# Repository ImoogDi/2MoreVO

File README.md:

#  2MoreVO
 Eurorack Dual VCO using the public CEM3340/AS3340 chip.

**Table of Contents**

- [Introduction](#intro)
- [Construction Guide](./doc/constructionguide.md)
- [Calibration](./doc/calibration.md)
- [Technical data](#technical-data)
- [References](#references)
- [License](#license)

## Introduction

This eurorack-modul is designed for modular-synthesizers as dual Voltage Controlled Oscillator.  
The oszillators are build around two IC's: <u>AS3340</u>, a clone of that wellknown CEM3340.  
Another benifit is the <u>three cannel VCA: AS3363</u> included to control the modulation-level, waveform output of VCO1 and oscillator-signal fading between VCO1- and VCO2-outputs.  

The '2MoreVO'-PCB's are:  
- one main backplane ('Backplane'), holding all switches, pots, jacks and voltage-references.  
- two VCO-PCB's stacked on the 'Backplane'.  
- one another backplane-PCB ('Backplane_B') hodling the 'three cannel VCA', operational-amp's and the eurorack-connection stacked on the 'Backplane'.   

All parts are common available and DIY-friendly designed, most parts are SMD on the VCO-PCB's.   
(Details see attached pictures)  

- Modul Frontpanel

<br>
- Modul Backpanel

<br>
- Modul function-blocks

<br>

<hr>
There are twelve 3.5mm jacks available for patching audio- and CV-signals.  

<table>
<tr>
    <th>Jack-Name</th>
    <th>Function</th>
    <th>Comment</th>
    <th>Detail</th>
</tr>
<tr>
    <td>1V/Oct CV1</td>
    <td>CV-input for VCO1 pitch control</td>
    <td>fixed 1Volt/Octave scaling</td>
    <td>This input is normalised with the eurobus Control-Voltage and connected with the '1V/Oct CV2' input.<br>Patch-cabel plugged in breaks the default connection to eurobus CV but the connection to '1V/Oct CV2' is still available.</td>
</tr>
<tr>
    <td>Fade CV</td>
    <td>CV-input for fading oscillator-signals</td>
    <td>The Fading between Osc1- and Osc2-signals on 'Osc-Mix Out' is controlled with this CV</td>
    <td>CV level adjustable between 0 ... max. with 'Fade CV'-pot.<br>works together with 'Osc-Fade'-pot.<hr>Bipolar signal input.</td>
</tr>
<tr>
    <td>Wave1 CV</td>
    <td>CV-input for VCO1 wave-control</td>
    <td>The waveform on 'Osc1 Out' is controlled with this CV</td>
    <td>CV Level adjustable between 0 ... max. with 'Wave1 CV'-pot.<hr>Bipolar signal input.</td>
</tr>
<tr>
    <td>Mod.Level CV</td>
    <td>CV-input for modulation level control</td>
    <td>Control of modulation level on 'Mod Out'</td>
    <td>Modulation Level adjustable between 0 ... max. with 'Mod.Level CV'-pot.<hr>Bipolar signal input.</td>
</tr>
<tr>
    <td>Mod. In</td>
    <td>Modulation signal input</td>
    <td>input for external signals controlling FM(Lin/Log) and PWM on Osc1 and Osc2</td>
    <td>This input is normalised with the sinusoidal-signal from Osc2 if no signal is plugged in.<hr>Bipolar signal input.</td>
</tr>
<tr>
    <td>1V/Oct CV2</td>
    <td>CV-input for VCO2 pitch control</td>
    <td>fixed 1Volt/Octave scaling</td>
    <td>This input is normalised with the '1V/Oct CV1' input.<br>Patch-cabel plugged in breaks the default connection to '1V/Oct CV1'.</td>
</tr>
<tr>
    <td>Osc1 Out</td>
    <td>output for VCO1-oscillator signal</td>
    <td>triangle- to saw-waveform output, morvable manually or with external CV</td>
    <td>Waveform morvable with 'Wave1 CV'-pot and CV-signal.</td>
</tr>
<tr>
    <td>Osc-Mix Out</td>
    <td>output for mixed VCO1-/VCO2-oscillator signal</td>
    <td>mixed signal from Osc1- and Osc2-outputs</td>
    <td>Waveforms fadeable between Osc1- and Osc2-signal outputs.<br>Fading can be done with 'Fade CV'-pot and CV-signal.<br>50%/50% Osc1/2-signal level on 'Osc-Mix Out', if 'Osc-Fade'-pot is in centerposition and no 'Fade CV' is plugged in.</td>
</tr>
<tr>
    <td>Osc2 Out</td>
    <td>output for VCO2-oscillator signal</td>
    <td>saw- to triangle-waveform output, morvable manually</td>
    <td>Waveform morvable with 'Wave2'-pot between saw- and triangle-signal.</td>
</tr>
<tr>
    <td>Sync In</td>
    <td>Sync-signal for VCO1 (optional VCO2)</td>
    <td>this signal can be switched to: 'Sync Hard', ' Sync Soft' or 'Off'</td>
    <td>This input is normalised with the 'Puls2 Out'-signal from VCO2.<br>Patch-cabel plugged in breaks the default connection to 'Puls2 Out'.</td>
</tr>
<tr>
    <td>Mod Out</td>
    <td>output for modulation-signal controllable with 'Mod.Level CV'</td>
    <td>modulation-signal used for 'FMx Lin/Log' and 'PWM'<br>default sinusoidal-signal from VCO2 used for VCO1 modulation</td>
    <td>sinusoidal-signal from VCO2 is available on this output if high impedance connection is used.<hr>optional an external low impedance signal plugged in can overwride the internal modulation.</td>
</tr>
<tr>
    <td>Puls2 Out</td>
    <td>output for puls-signal from VCO2</td>
    <td>output-signal for synchronisation and audio<br>the pulswith is controllable with 'PWM'-pot using the 'Mod Out'-signal</td>
    <td>This output is also internally linked to 'Sync In'.<hr>Bipolar output with +-5.0Volt level.</td>
</tr>
</table>
<br>

There are eight potentiometers with following functions:  

<table>
<tr>
    <th>Pot-Name</th>
    <th>Function</th>
    <th>Comment</th>
    <th>Detail</th>
</tr>
<tr>
    <td>Tune 1</td>
    <td>Pitch for VCO1</td>
    <td>default pitch in center-position</td>
    <td>tuning-range +-2 octaves.</td>
</tr>
<tr>
    <td>Tune 2</td>
    <td>Pitch for VCO2</td>
    <td>default pitch in center-position</td>
    <td>tuning-range +-2 octaves.</td>
</tr>
<tr>
    <td>Osc-Fade</td>
    <td>manually fading between Osc1- and Osc2-signals on 'Osc-Mix Out'</td>
    <td>works as CV offset for the 'Fade CV'-signal</td>
    <td>pot to CCW: Osc2-signal output.<br>pot to CW: Osc1-signal output.<br>pot to centerposition: equal level output.</td>
</tr>
<tr>
    <td>Fade CV</td>
    <td>CV Level amount pot for fading between Osc1- and Osc2-signals on 'Osc-Mix Out'</td>
    <td>works together with 'Osc-Fade' for fading Osc1/2-signals</td>
    <td>CV Level adjustable between 0 ... max.</td>
</tr>
<tr>
    <td>Wave1 CV</td>
    <td>CV Level amount pot for Osc1 waveform-selection on 'Osc1 out'</td>
    <td>manually selection of waveform is possible if no CV-signal is plugged in</td>
    <td>CV Level adjustable between 0 ... max.</td>
</tr>
<tr>
    <td>Mod.Level CV</td>
    <td>CV Level amount pot for modulation control</td>
    <td>manually modulationlevel control is possible if no CV-signal is plugged in</td>
    <td>CV Level adjustable between 0 ... max.</td>
</tr>
<tr>
    <td>PWM</td>
    <td>pulswith pot to control amount of PWM</td>
    <td>the modulation-signal on 'Mod Out' is used for PWM</td>
    <td>PWM amount adjustable between 0 ... max.<br>Pulswith is 50% on 'Puls2 Out' if pot is in CCW-position (set to 0).</td>
</tr>
<tr>
    <td>Wave2</td>
    <td>waveform selection pot for Osc2-signal</td>
    <td>manually morving between saw- and triangle-signal</td>
    <td>pot to CCW: SAW-signal.<br>pot to CW: Triangle-signal.<br>pot to centerposition: mixed signal.</td>
</tr>
</table>
<br>

There are six switches to control the behaviour of signals.  

<table>
<tr>
    <th>Switch</th>
    <th>Function</th>
    <th>Comment</th>
    <th>Detail</th>
</tr>
<tr>
    <td>FM1-switch</td>
    <td>switch for VCO1 FM modulation using signal on 'Mod Out'</td>
    <td>FM controll for VCO1</td>
    <td>FM1 Lin := Linear FM modulation.<br>Off := function off.<br>FM1 Log := Logarithmic FM modulation.</td>
</tr>
<tr>
    <td>Sync-switch</td>
    <td>switch for VCO1 Hard- or Soft-synchronisation with puls-signal from VCO2</td>
    <td>switched synchronisation-signal from 'Puls2 Out'</td>
    <td>Sync Hard := hard synced to VCO2.<br>Off := sync. function off.<br>Sync Soft := soft synced to VCO2.</td>
</tr>
<tr>
    <td>VCO1 Octave-switch</td>
    <td>switch for VCO1 pitch setting</td>
    <td>octaves up or down depending on 'Octave switch + or -'</td>
    <td>1 := one octave (up/down).<br>2 := two octaves (up/down).</td>
</tr>
<tr>
    <td>Octave up/down switch</td>
    <td>switch for VCO1- and VCO2-switched pitchcontrol</td>
    <td>selecting pitch up or down for VCO1 and VCO2</td>
    <td>+ :=  pitch up.<br>- := pitch down.</td>
</tr>
<tr>
    <td>VCO2 Octave-switch</td>
    <td>switch for VCO2 pitch setting</td>
    <td>octaves up or down depending on 'Octave switch + or -'</td>
    <td>1 := one octave (up/down).<br>2 := two octaves (up/down).</td>
</tr>
<tr>
    <td>FM2-switch</td>
    <td>switch for VCO2 FM modulation using signal on 'Mod Out'</td>
    <td>FM controll for VCO2</td>
    <td>FM1 Lin := Linear FM modulation.<br>Off := function off.<br>FM1 Log := Logarithmic FM modulation.</td>
</tr>
</table>
<br>
<hr>

## Technical data

- size:  
  width: 16HP  
  depth: 45mm

- power:  
    5Volt, 0 mA  
  +12Volt, 60mA  
  -12Volt, 60mA  

- frequency range: 20Hz to 20kHz.
- frequency CV scale: 1V/Oct on '1V/Oct CV1'- and '1V/Oct CV2'-inputs.
- frequency pot tuning range: +-2 Octaves.
- frequency switchable pitch range: plus or minus 1 or 2 octaves for oscillator 1/2.
- signal inputs, DC-coupled signal path.
- signal outputs, DC-coupled signal path.
- signal input impedance: > 50kOhm.
- signal output impedance: 500 Ohm.
- expandable with more '2MoreVO' dual-oscillator('s) used in master-/slave-configuration.

## References

* [electric druid, Single VCA crossfader](https://electricdruid.net/single-vca-crossfader/)
* [Tuning the AS3340](https://www.alfarzpp.lv/eng/sc/Tuning%20the%20AS3340.pdf)

## License
> Hardware:cc by-nc-sa 4.0  ([details](https://creativecommons.org/licenses/by-nc-sa/4.0/))

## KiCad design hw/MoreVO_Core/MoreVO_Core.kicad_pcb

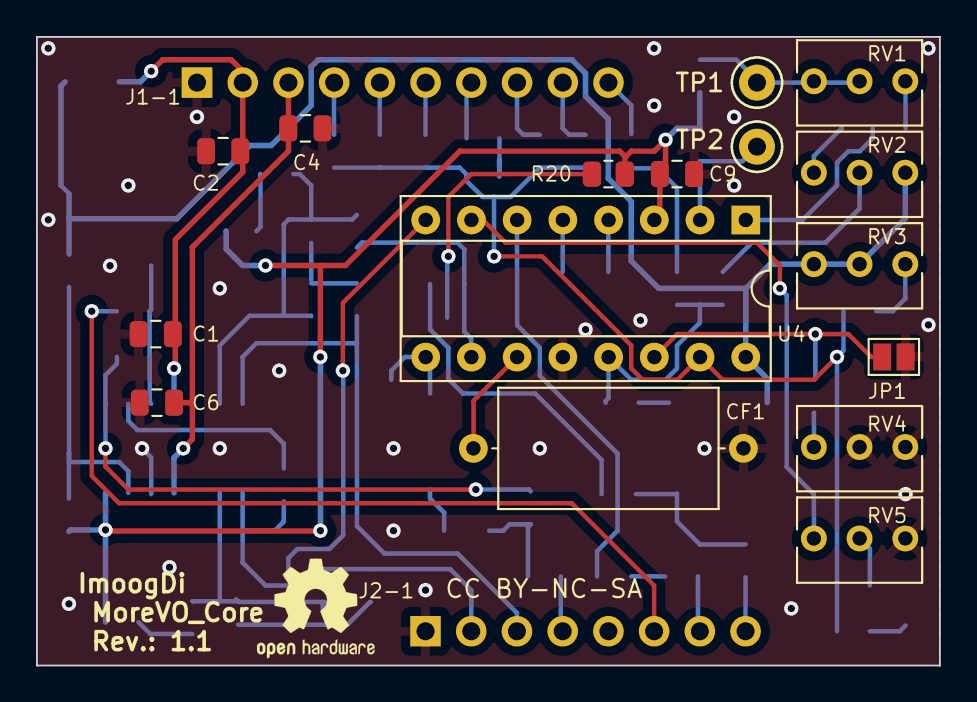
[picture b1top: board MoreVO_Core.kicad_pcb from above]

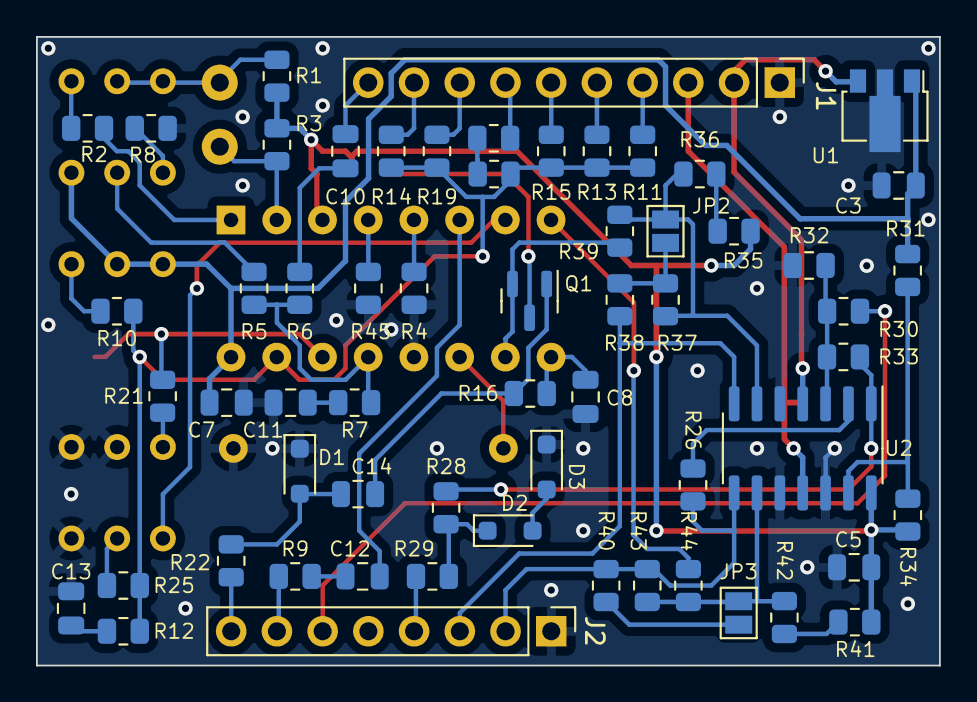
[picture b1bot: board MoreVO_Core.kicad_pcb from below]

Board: 2 copper layers, 50.2 x 34.9 mm, 76 parts (60 on the bottom side), 58 nets.

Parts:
C1, C5, C6, C7, C8, C9, C10: 100nF; C_0805_2012Metric
C2, C3: 1000nF; C_0805_2012Metric
C4: 330nF; C_0805_2012Metric
C11, C13: 10nF; C_0805_2012Metric
C12: 1nF; C_0805_2012Metric
C14: 220pF; C_0805_2012Metric
CF1: 1nF; C_Axial_L12.0mm_D6.5mm_P15.00mm_Horizontal
D1: 1N4148; D_SOD-323_HandSoldering
D2, D3: BZX 384 4.7V; D_SOD-323_HandSoldering
J1: Conn_01x10; PinHeader_1x10_P2.54mm_Vertical
J2: Conn_01x08; PinHeader_1x08_P2.54mm_Vertical
JP1, JP2, JP3: Jumper_2_Open; SolderJumper-2_P1.3mm_Open_Pad1.0x1.5mm
Q1: MMBT3906; SOT-23
R1, R3: 5.6K; R_0805_2012Metric
R2, R8, R31: 20K; R_0805_2012Metric
R4, R22, R26, R28, R30, R34: 10K; R_0805_2012Metric
R5, R6, R25, R33: 1M; R_0805_2012Metric
R7, R12: 470; R_0805_2012Metric
R9, R29: 1K; R_0805_2012Metric
R10: 120K; R_0805_2012Metric
R11, R13, R14, R15, R17, R18, R19: 100K 0.1%; R_0805_2012Metric
R16: 47K; R_0805_2012Metric
R20: 100; R_0805_2012Metric
R21: 1.5K; R_0805_2012Metric
R32, R39, R44: 100K; R_0805_2012Metric
R35, R36, R37, R38, R40, R41, R43: 150K; R_0805_2012Metric
R42: 0R; R_0805_2012Metric
R45: 51K; R_0805_2012Metric
RV1, RV2: 10K; Potentiometer_Bourns_3266Y_Vertical
RV3: 100K; Potentiometer_Bourns_3266Y_Vertical
RV4: 500; Potentiometer_Bourns_3266Y_Vertical
RV5: 20K; Potentiometer_Bourns_3266Y_Vertical
TP1, TP2: TestPoint; TestPoint_Keystone_5000-5004_Miniature
U1: MCP1804x-1802xDB; SOT-89-3
U2: TL074; SOIC-14_3.9x8.7mm_P1.27mm
U4: AS3340; DIP-16_W7.62mm_Socket

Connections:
+10V: C3.2, C7.2, R31.1, RV2.1, RV3.2, RV3.3, U1.1 (OUT), U4.16 (VCC)
+12V: C1.2, C2.2, J1.2, U1.3 (IN), U2.4 (V+)
-5V: C5.2, C9.2, R1.1, R3.1, R20.1, R34.2, R35.1, R41.1, U2.14, U4.3 (VEE)
-12V: C4.2, C6.1, J1.3, U2.11 (V-)
/Input_Conditioner/1V/Oct.: J1.6, R15.1
/Input_Conditioner/FM Log: J1.9, R14.1
/Input_Conditioner/Hard Sync: C12.2, U4.6 (VHSI)
/Input_Conditioner/High Freq Track: RV5.3, U4.7 (VHFT)
/Input_Conditioner/Linear FM: R5.2, R6.1, R7.2, U4.13 (VLFI)
/Input_Conditioner/Linear FM In: C10.2, J1.10
/Input_Conditioner/Oct.1: J1.7, R17.1
/Input_Conditioner/Oct.2: J1.8, R19.1
/Input_Conditioner/PWM Control: R4.2, U4.5 (VPWM)
/Input_Conditioner/Scale: JP1.1 (A), R21.2, U4.14 (VS)
/Input_Conditioner/Scale Adj. 1: R2.2, U4.1 (SCALE1)
/Input_Conditioner/Scale Adj. 2: R3.2, TP2.1, U4.2 (SCALE2)
/Input_Conditioner/Tune: J1.4, R11.1
/Input_Conditioner/Tune2: J1.5, R13.1
/Output_Conditioner/PWM_CTRL: J2.6, R30.1
/Output_Conditioner/Puls: R45.1, U4.4 (VP)
/Output_Conditioner/Puls_Out: J2.4, R29.2
/Output_Conditioner/SAW: R44.1, U4.8 (VSO)
/Output_Conditioner/SAW_Out: J2.2, R26.1, R40.2, R43.2, U2.8
/Output_Conditioner/TRI_Out: J2.3, R38.2, U2.7
/Uref: C8.2, R16.2, U4.9 (VSSI)
Freq. Control: R10.2, R11.2, R12.2, R13.2, R14.2, R15.2, R18.2, R19.2, R25.2, U4.15 (VFCI)
GND: C1.1, C2.1, C3.1, C4.1, C5.1, C6.2, C7.1, C8.1, C9.1, C11.1, C13.1, CF1.2, D1.1 (K), D3.1 (K), J1.1, J2.1, JP1.2 (B), R4.1, R8.1, R32.1, R45.2, RV4.1, RV4.2, RV5.1, U1.2 (GND), U2.5 (+), U2.10 (+), U2.12 (+), U4.12 (GND)
unnamed: C10.1, R6.2
unnamed: C11.2, R7.1
unnamed: C12.1, R9.2
unnamed: C13.2, R12.1
unnamed: C14.2, D1.2 (A), R22.2
unnamed: D2.2 (A), D3.2 (A)
unnamed: D2.1 (K), R28.2, R29.1
unnamed: JP2.1 (A), R37.2, R38.1
unnamed: JP2.2 (B), R36.2, R37.1, R39.2, U2.6 (-)
unnamed: JP3.1 (A), R40.1
unnamed: JP3.2 (B), R42.2, R43.1, R44.2, U2.9 (-)
unnamed: C14.1, Q1.1 (B), R16.1
unnamed: Q1.3 (C), R20.2
unnamed: R1.2, RV1.2, RV1.3, TP1.1
unnamed: R2.1, RV1.1
unnamed: R5.1, RV2.2
unnamed: R8.2, RV2.3
unnamed: R10.1, RV3.1
unnamed: R17.2, R18.1
unnamed: R21.1, RV4.3
unnamed: R25.1, RV5.2
unnamed: R28.1, R33.1, U2.1
unnamed: R35.2, R36.1
unnamed: R41.2, R42.1
unnamed: R30.2, R32.2, R33.2, U2.3 (+)
unnamed: R26.2, U2.2 (-)
unnamed: R31.2, R34.1, U2.13 (-)
unnamed: CF1.1, U4.11 (CAP)
Sync_Hard: J2.7, R9.1
Sync_Soft: J2.8, R22.1
TRI: Q1.2 (E), R39.1, U4.10 (VTO)

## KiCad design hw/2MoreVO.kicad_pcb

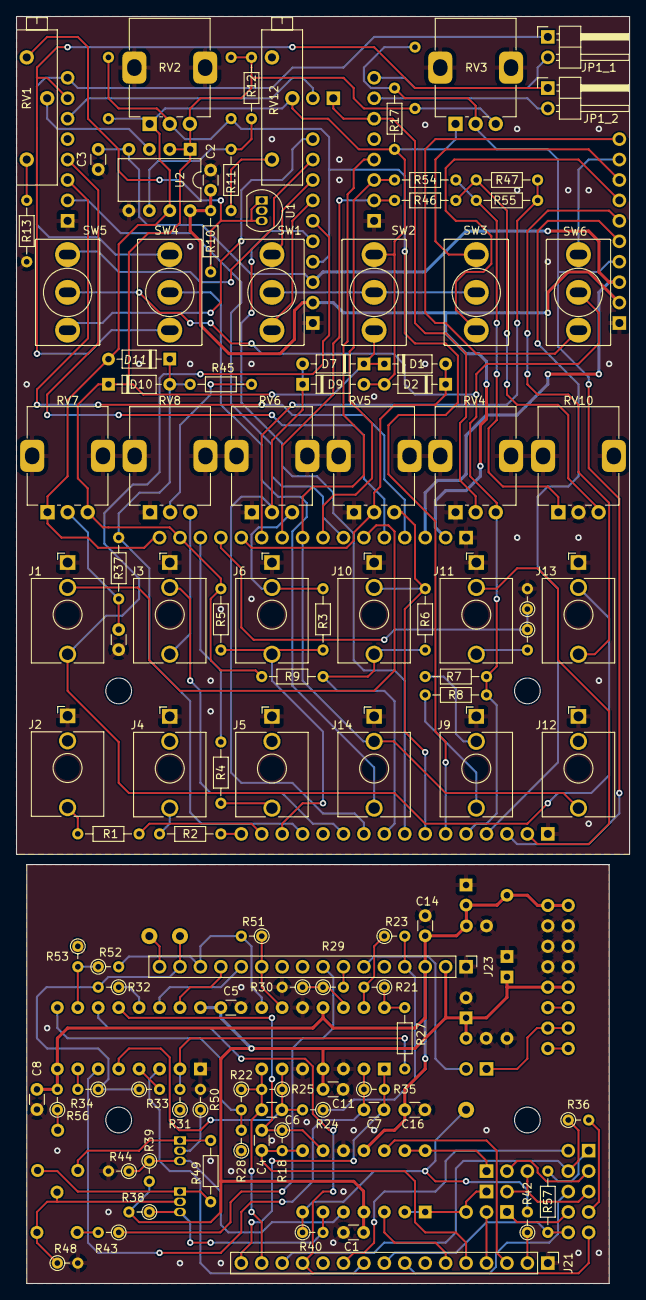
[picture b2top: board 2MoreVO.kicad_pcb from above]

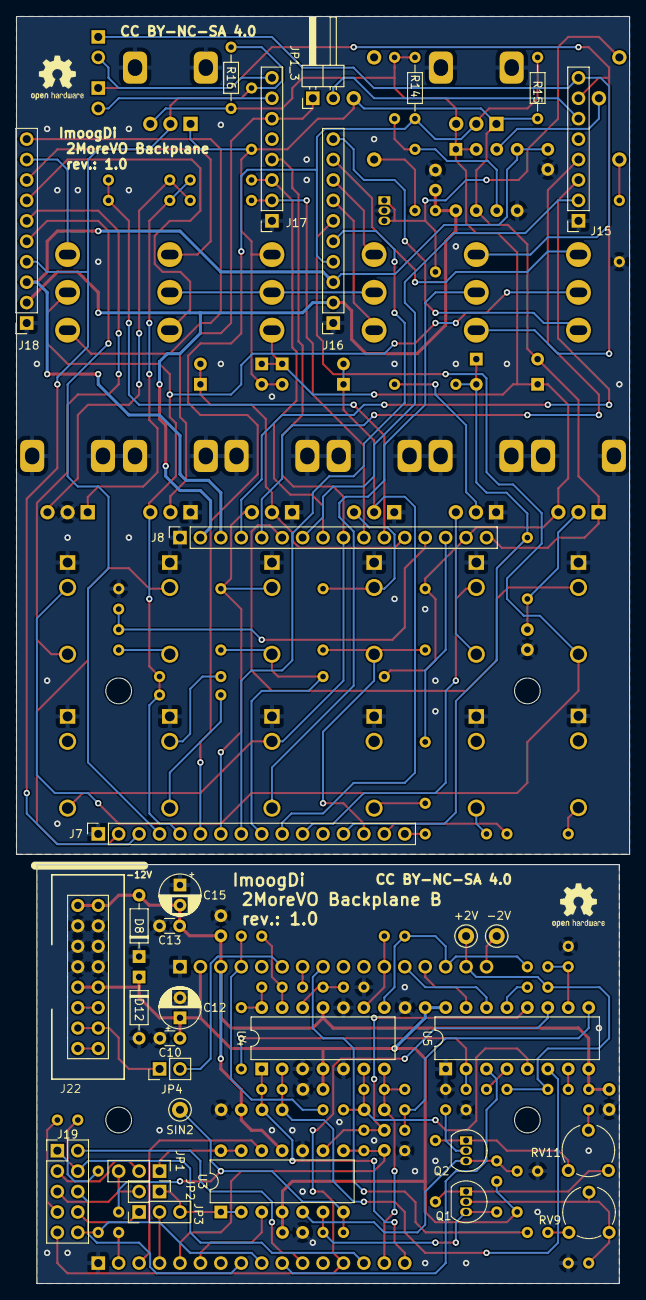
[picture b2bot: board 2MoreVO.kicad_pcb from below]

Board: 2 copper layers, 76.2 x 157.5 mm, 142 parts (34 on the bottom side), 122 nets.

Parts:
C1, C2, C3, C5, C8, C9, C10, C11, C13, C14, C16: 100nF; C_Disc_D3.0mm_W1.6mm_P2.50mm
C4, C6, C7: 27pF; C_Disc_D3.0mm_W1.6mm_P2.50mm
C12, C15: 22u; CP_Radial_D5.0mm_P2.50mm
D1, D2, D7, D9, D10, D11: BAT46; D_DO-35_SOD27_P7.62mm_Horizontal
D8, D12: 1N4001; D_DO-35_SOD27_P7.62mm_Horizontal
J1, J2, J3, J4, J5, J6, J9, J10, J11, J12, J13, J14: AudioJack2_SwitchT; Jack_3.5mm_QingPu_WQP-PJ398SM_Vertical_CircularHoles
J7, J8: Conn_01x16_Socket; PinSocket_1x16_P2.54mm_Vertical
J15, J17: Conn_01x08_Socket; PinSocket_1x08_P2.54mm_Vertical
J16, J18: Conn_01x10_Socket; PinSocket_1x10_P2.54mm_Vertical
J19: Conn_02x05_Odd_Even; PinHeader_2x05_P2.54mm_Vertical
J21, J23: Conn_01x16_Pin; PinHeader_1x16_P2.54mm_Vertical
J22: Conn_02x08_Odd_Even; Pins_2x08_2.54mm_TH_EuroPower_Shrouded_reducedsilk_pins_ass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
JP1, JP3: Jumper_3_Open; PinHeader_1x03_P2.54mm_Vertical
JP1_1, JP1_2, JP1_3: Jumper_2_Open; PinHeader_1x02_P2.54mm_Horizontal
JP2: Jumper_2_Open; PinHeader_1x02_P2.54mm_Vertical
JP4: Jumper_2_Bridged; PinHeader_1x02_P2.54mm_Vertical
Q1, Q2: 2N3904; TO-92_Inline
R1, R2, R4: 470; R_Axial_DIN0204_L3.6mm_D1.6mm_P7.62mm_Horizontal
R3, R6, R45: 100K; R_Axial_DIN0204_L3.6mm_D1.6mm_P7.62mm_Horizontal
R5, R9, R10, R12, R13, R57: 10K; R_Axial_DIN0204_L3.6mm_D1.6mm_P7.62mm_Horizontal
R7: 1K; R_Axial_DIN0204_L3.6mm_D1.6mm_P7.62mm_Horizontal
R8: 2,7K; R_Axial_DIN0204_L3.6mm_D1.6mm_P7.62mm_Horizontal
R11: 6,8K; R_Axial_DIN0204_L3.6mm_D1.6mm_P7.62mm_Horizontal
R14, R15, R16, R17: 27K(15K); R_Axial_DIN0204_L3.6mm_D1.6mm_P7.62mm_Horizontal
R18, R21, R30, R35: 47K; R_Axial_DIN0204_L3.6mm_D1.6mm_P2.54mm_Vertical
R19, R22, R52: 150K; R_Axial_DIN0204_L3.6mm_D1.6mm_P2.54mm_Vertical
R20, R28, R31, R48, R50, R53: 1K; R_Axial_DIN0204_L3.6mm_D1.6mm_P2.54mm_Vertical
R23, R24, R25, R29, R51: 100K; R_Axial_DIN0204_L3.6mm_D1.6mm_P2.54mm_Vertical
R27: 150K; R_Axial_DIN0204_L3.6mm_D1.6mm_P7.62mm_Horizontal
R32, R33, R34: 2.7K; R_Axial_DIN0204_L3.6mm_D1.6mm_P2.54mm_Vertical
R36, R38, R39, R40, R44: 10K; R_Axial_DIN0204_L3.6mm_D1.6mm_P2.54mm_Vertical
R37: 51K; R_Axial_DIN0204_L3.6mm_D1.6mm_P7.62mm_Horizontal
R42: 470; R_Axial_DIN0204_L3.6mm_D1.6mm_P2.54mm_Vertical
R43, R56: 20K; R_Axial_DIN0204_L3.6mm_D1.6mm_P2.54mm_Vertical
R46, R47, R54, R55: 47K; R_Axial_DIN0204_L3.6mm_D1.6mm_P7.62mm_Horizontal
R49: 390; R_Axial_DIN0204_L3.6mm_D1.6mm_P7.62mm_Horizontal
REF_A: OSHW-Logo2_7.3x6mm_SilkScreen
REF_B: OSHW-Logo2_7.3x6mm_SilkScreen
REF_L1, REF_L2, REF_L3, REF_L4: MountingHole_3.2mm_M3
RV1, RV12: 5K; Potentiometer_Bourns_3006P_Horizontal
RV2, RV3: 100K(50K) lin.; Potentiometer_Alps_RK09K_Single_Vertical
RV4, RV5, RV6, RV7, RV8, RV10: 100K; Potentiometer_Alps_RK09K_Single_Vertical
RV9: 50K; Potentiometer_Piher_PT-6-V_Vertical
RV11: 10K; Potentiometer_Piher_PT-6-V_Vertical
SW1, SW3, SW4, SW5, SW6: SW_SPDT_MSM; Switch_Toggle_SPDT_Mini_SolderLug
SW2: SW_SPDT; Switch_Toggle_SPDT_Mini_SolderLug
TP1: +2V; TestPoint_Keystone_5000-5004_Miniature
TP2: -2V; TestPoint_Keystone_5000-5004_Miniature
TP3: SIN2; TestPoint_Keystone_5000-5004_Miniature
U1: TL431LP; TO-92_Inline
U2: TL072; DIP-8_W7.62mm
U3, U4: TL074; DIP-14_W7.62mm
U5: AS3363; DIP-16_W7.62mm

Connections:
+2.0VRef: D1.1 (K), D7.1 (K), D10.1 (K), J8.15, R5.2, R9.2, R12.1, R14.1, R16.1, RV2.3, RV3.3, RV7.3, SW2.3 (C), U2.1, U2.2 (-)
+12V: C2.1, J8.2, J16.2, J18.2, R10.1, U2.8 (V+)
+12VA: C1.1, C5.1, C10.1, C11.1, C12.1, D12.1 (K), J22.9, J22.10, J23.2, R38.2, R39.2, U3.4 (V+), U4.4 (V+), U5.16 (VCC)
-2.0VRef: D2.2 (A), D9.2 (A), D11.2 (A), J8.16, R15.2, R17.2, RV2.1, RV3.1, RV7.1, RV12.2, SW2.1 (A), U2.7
-12V: C3.2, J8.3, J16.3, J18.3, U2.4 (V-)
-12VA: C8.1, C13.2, C14.2, C15.2, C16.2, D8.2 (A), J22.1, J22.2, J23.3, R56.2, U3.11 (V-), U4.11 (V-), U5.8 (VEE)
/ModSyn.Level_CV: J7.7, J10.TN, R6.1, RV5.3
/ModSyn.Mod_In: J11.T, R19.2
/ModSyn.Mod_Out: J7.5, R7.1, R8.1, RV4.3, SW5.2, SW6.2
/ModSyn.Sync_In: J14.T, SW4.2
/VCO1.FM_Lin: J16.10, SW5.3
/VCO1.FM_Log: J16.9, SW5.1
/VCO1.Oct1: J16.7, SW1.1
/VCO1.Oct2: J16.8, SW1.3
/VCO1.PULS: J8.5, J15.4
/VCO1.PWM_ctrl: J15.6, JP1_3.2 (B)
/VCO1.SAW: J8.7, J15.2
/VCO1.Sync_Hard: J15.7, JP1_2.1 (A), SW4.3
/VCO1.Sync_Soft: J15.8, JP1_1.1 (A), SW4.1
/VCO1.TRI: J8.4, J15.3
/VCO1.Tune: J7.6, J16.4, R14.2, R15.1, RV2.2
/VCO1.Tune2: J7.8, J16.5
/VCO2.1V_Oct: J13.T, J18.6
/VCO2.FM_Lin: J18.10, SW6.3
/VCO2.FM_Log: J18.9, SW6.1
/VCO2.Oct1: J18.7, SW3.1
/VCO2.Oct2: J18.8, SW3.3
/VCO2.PULS: J8.9, J12.T, J14.TN, J17.4
/VCO2.PWM_ctrl: J17.6, JP1_3.1 (A), RV4.2
/VCO2.SAW: J8.10, J17.2, R46.1
/VCO2.Sync_Hard: J17.7, JP1_2.2 (B)
/VCO2.Sync_Soft: J17.8, JP1_1.2 (B)
/VCO2.TRI: J8.8, J17.3, R54.1
/VCO2.Tune: J7.3, J18.4, R16.2, R17.1, RV3.2
/VCO2.Tune2: J7.4, J18.5
CV_Bus: J1.TN, J8.6
CV_VCO_Fader: D10.2 (A), D11.1 (K), J7.13, R37.1, R45.1
Fade_CV: J3.T, RV8.3
Fade_CV_Ext: J3.TN, J7.11
Fader_Out: C7.1, R35.1, U4.2 (-), U5.6 (Iout3)
Former_In: R27.2, R31.2, U5.2 (In1)
Former_Out: C6.1, R24.2, R25.1, U4.6 (-), U5.5 (Iout1)
GND: C2.2, C3.1, C9.2, J1.S, J2.S, J3.S, J4.S, J5.S, J6.S, J7.1, J8.1, J9.S, J10.S, J11.S, J12.S, J13.S, J14.S, J15.1, J16.1, J17.1, J18.1, R13.1, R20.2, RV2.MP (MountPin), RV3.MP (MountPin), RV4.1, RV4.MP (MountPin), RV5.1, RV5.MP (MountPin), RV6.1, RV6.MP (MountPin), RV7.MP (MountPin), RV8.1, RV8.MP (MountPin), RV10.2, RV10.MP (MountPin), U1.2 (A), U2.5 (+)
GNDA: C1.2, C5.2, C8.2, C10.2, C11.2, C12.2, C13.1, C14.1, C15.1, C16.1, D8.1 (K), D12.2 (A), J21.1, J22.3, J22.4, J22.5, J22.6, J22.7, J22.8, J23.1, R28.1, R30.2, R31.1, R44.2, R48.2, R50.2, R53.1, U3.10 (+), U4.3 (+), U4.5 (+), U4.10 (+), U5.1 (GND)
Mod_Level_CV_Ext: J7.9, J10.T, R6.2, R9.1
unnamed: C9.1, R37.2, RV7.2
unnamed: J2.T, R1.1
unnamed: J4.T, R2.1
unnamed: J5.T, R4.1
unnamed: J9.T, R8.2
unnamed: J9.TN, R7.2
unnamed: J19.1, R57.1
unnamed: J19.3, JP1.2 (C)
unnamed: J19.5, JP1.3 (B), JP2.2 (B)
unnamed: J19.7, R36.2
unnamed: J19.8, JP3.1 (A)
unnamed: J22.11, J22.12
unnamed: J22.13, J22.14, JP4.1 (A)
unnamed: J22.15, J22.16
unnamed: JP1.1 (A), U3.13 (-), U3.14
unnamed: JP2.1 (A), JP3.3 (B), U3.1, U3.2 (-)
unnamed: Q1.2 (B), R48.1, RV9.1, RV9.2
unnamed: Q1.3 (C), R38.1, R40.2, U3.6 (-)
unnamed: Q1.1 (E), R49.1, RV11.1
unnamed: Q2.2 (B), R50.1
unnamed: Q2.3 (C), R39.1, R44.1, U3.5 (+)
unnamed: Q2.1 (E), R49.2, RV11.3
unnamed: R11.2, RV12.1
unnamed: R13.2, RV1.1
unnamed: R21.1, R27.1, U4.14
unnamed: R40.1, R42.2, TP3.1, U3.7
unnamed: R43.2, RV9.3
unnamed: R45.2, RV8.2
unnamed: R46.2, R47.1, RV10.3
unnamed: R54.2, R55.1, RV10.1
unnamed: R56.1, RV11.2
unnamed: SW1.2, SW2.2 (B), SW3.2
unnamed: R10.2, RV1.3, U1.1 (REF), U1.3 (K)
unnamed: RV1.2, U2.3 (+)
unnamed: R11.1, R12.2, U2.6 (-)
unnamed: R29.1, R30.1, U4.12 (+)
unnamed: R21.2, R23.1, U4.13 (-)
unnamed: R33.2, U5.4 (Vcntrl1)
unnamed: R32.1, U5.13 (Vcntrl2)
unnamed: R34.2, U5.7 (Vcntrl3)
OSC1_Out: J7.15, R1.2
OSC2_Out: J8.14, R4.2
OSC_Mix_Out: J7.16, R2.2
Pin_+2.0VRef: J23.15, R32.2, R33.1, R34.1, TP1.1
Pin_-2.0VRef: J23.16, TP2.1
Pin_CV_Bus: J23.6, JP4.2 (B)
Pin_CV_VCO_Fader: J19.9, J21.13, U5.11 (CVMix3)
Pin_Fade_CV_Ext: J19.2, J21.11
Pin_Mod_Level_CV_Ext: J19.10, J21.9, R57.2
Pin_Mod_Out: C4.2, J21.5, R18.2, U3.8
Pin_OSC1_Out: C6.2, J21.15, R22.1, R25.2, U4.7
Pin_OSC2_Out: J23.14, R51.2, R52.2, U4.8
Pin_OSC_Mix_Out: C7.2, J21.16, R35.2, U4.1
Pin_SAW1: J23.7, R29.2
Pin_SIN2: J21.2, R42.1
Pin_TRI1: J23.4, R23.2, R24.1
Pin_TRI2: J23.8, R43.1
Pin_Tune2VCO1: J19.6, J21.8
Pin_Tune2VCO2: J21.4, JP3.2 (C)
Pin_TuneVCO1: J21.6, U3.3 (+)
Pin_TuneVCO2: J21.3, U3.12 (+)
Pin_VCA_Level_CV: J23.12, U5.14 (CVMix2)
Pin_VCA_Mod_In: J23.13, U5.15 (In2)
Pin_Wave1_CV: J21.10, U5.3 (CVMix1)
Pin_Wave1_CV_In_Ext: J19.4, J21.14, R36.1
Pin_Wave2_Fade: J23.11, R51.1, U4.9 (-)
SIN2: J7.2, J11.TN
VCA_Level_CV: D1.2 (A), D2.1 (K), J8.12, RV5.2
VCA_Mod_In: J8.13, R19.1, R20.1
VCA_Out: C4.1, R18.1, U3.9 (-), U5.12 (Iout2)
VCO1_1V_Oct: J1.T, J13.TN, J16.6
Wave1: R22.2, R28.2, U5.9 (In3A)
Wave1_CV: D7.2 (A), D9.1 (K), J7.10, RV6.2
Wave1_CV_In: J6.TN, R3.1, RV6.3
Wave1_CV_In_Ext: J6.T, J7.14, R3.2, R5.1
Wave2: R52.1, R53.2, U5.10 (In3B)
Wave2_Fade: J8.11, R47.2, R55.2

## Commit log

2024-07-19 Add files via upload
    update readme
2024-07-19 Add files via upload
    2MoreVO; rev: 1.0
2024-07-23 Add files via upload
    MoreVO_Core rev.: 1.1 added
2024-07-24 Add files via upload
    MoreVO_Core PCB pictures added.
2024-07-29 doc and pic's update
2024-08-10 doc-calibration update
2024-08-10 doc-update
